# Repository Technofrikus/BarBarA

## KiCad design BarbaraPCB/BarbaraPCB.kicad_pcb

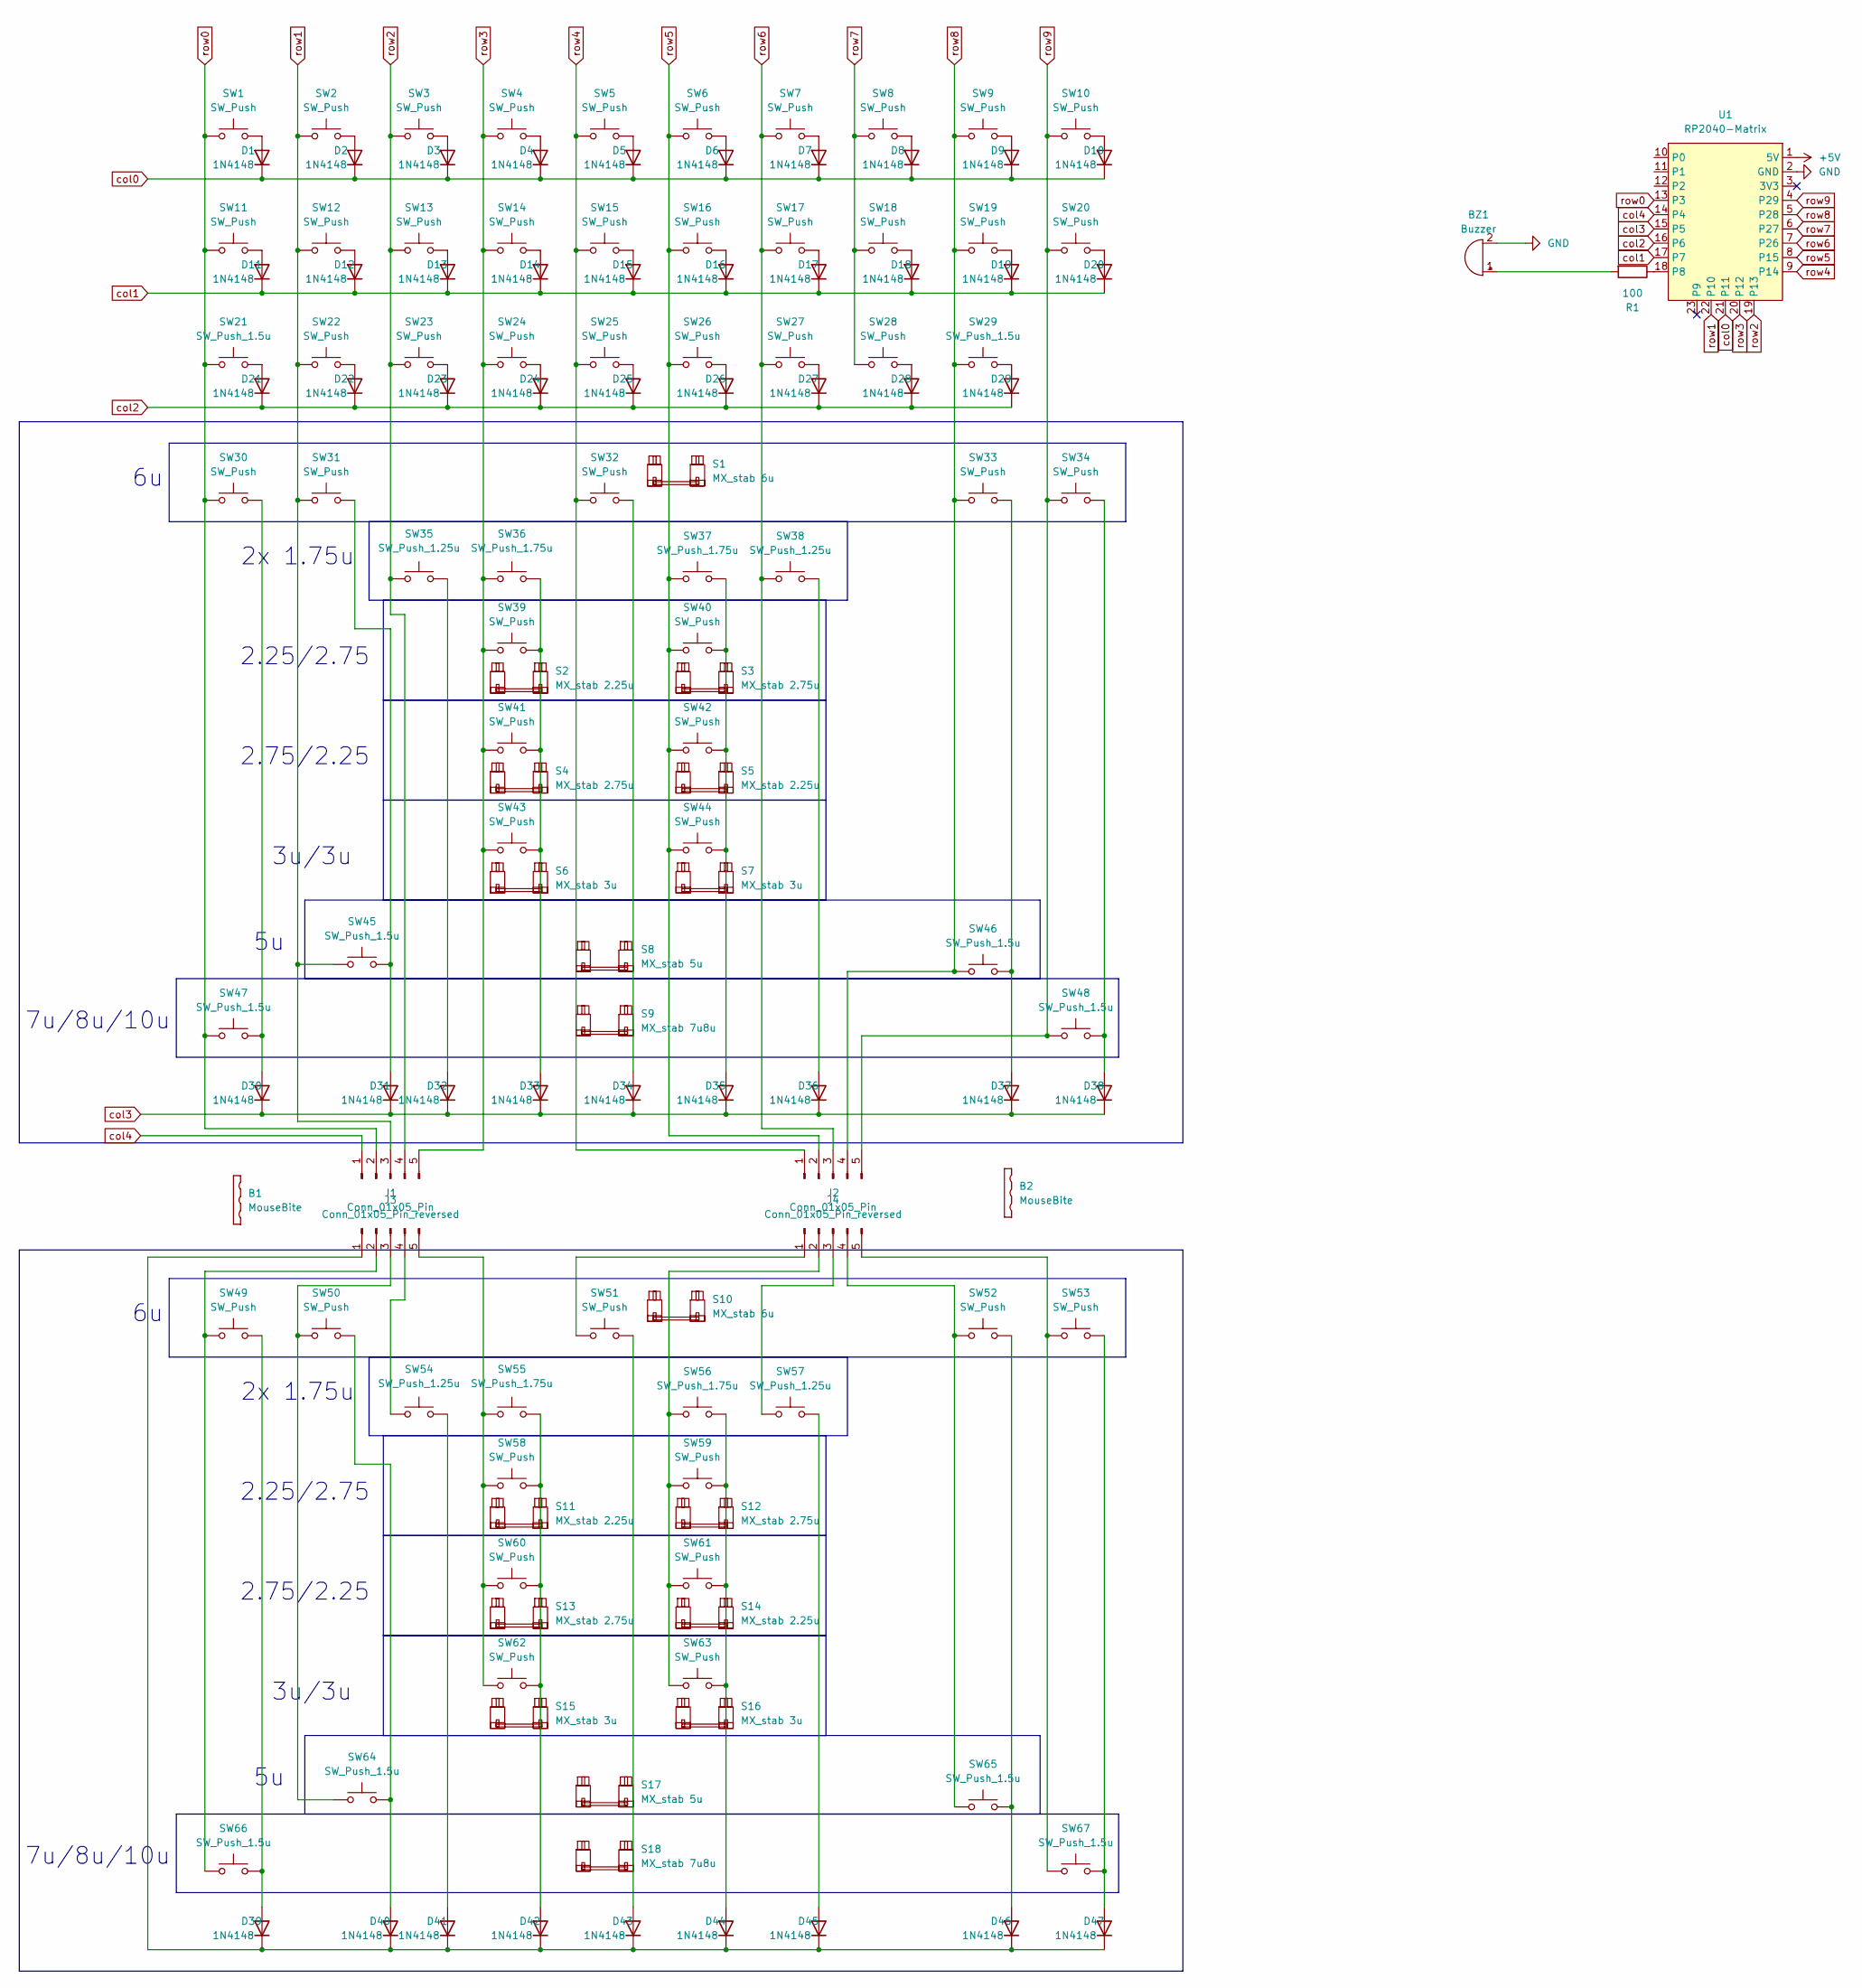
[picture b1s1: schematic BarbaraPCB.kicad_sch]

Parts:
B1, B2: MouseBite; TFmousebites_easysnap
BZ1: Buzzer; MagneticBuzzer_StarMicronics_QMB-105
D1, D2, D3, D4, D5, D6, D7, D8, D9, D10, D11, D12, D13, D14, D15, D16, D17, D18, D19, D20, D21, D22, D23, D24, D25, D26, D27, D28, D29, D30, D31, D32, D33, D34, D35, D36, D37, D38, D39, D40, D41, D42, D43, D44, D45, D46, D47: 1N4148; Diode-dual
J1, J2: Conn_01x05_Pin; PinSocket_1x05_P2.54mm_Vertical
J3, J4: Conn_01x05_Pin_reversed; PinSocket_1x05_P2.54mm_Vertical
R1: 100; Resistor-dual
S1, S10: MX_stab 6u; STAB_MX_P_6u_sizelabel
S2, S5, S11, S14: MX_stab 2.25u; STAB_MX_P_2.25u_sizelabel
S3, S4, S12, S13: MX_stab 2.75u; STAB_MX_P_2.75u_sizelabel
S6, S7, S15, S16: MX_stab 3u; STAB_MX_3u_sizelabel
S8, S17: MX_stab 5u; STAB_MX_5u
S9, S18: MX_stab 7u8u; STAB_MX_P_10u_sizelabel
SW1, SW2, SW3, SW4, SW5, SW6, SW7, SW8, SW9, SW10, SW11, SW12, SW13, SW14, SW15, SW16, SW17, SW18, SW19, SW20, SW22, SW23, SW24, SW25, SW26, SW27, SW28, SW30, SW31, SW32, SW33, SW34, SW39, SW40, SW41, SW42, SW43, SW44, SW49, SW50, SW51, SW52, SW53, SW58, SW59, SW60, SW61, SW62, SW63: SW_Push; SW_MX_1u
SW21, SW29, SW45, SW46, SW47, SW48, SW64, SW65, SW66, SW67: SW_Push_1.5u; SW_MX_1.5u
SW35, SW38, SW54, SW57: SW_Push_1.25u; SW_MX_1.25u
SW36, SW37, SW55, SW56: SW_Push_1.75u; SW_MX_1.75u
U1: RP2040-Matrix; RP2040-Gemini-BigHole

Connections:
+5V: U1.1 (5V)
GND: BZ1.2 (-), U1.2 (GND)
unnamed: BZ1.1 (+), R1.2
unnamed: D1.2 (A), SW1.2
unnamed: D2.2 (A), SW2.2
unnamed: D3.2 (A), SW3.2
unnamed: D4.2 (A), SW4.2
unnamed: D5.2 (A), SW5.2
unnamed: D6.2 (A), SW6.2
unnamed: D7.2 (A), SW7.2
unnamed: D8.2 (A), SW8.2
unnamed: D9.2 (A), SW9.2
unnamed: D10.2 (A), SW10.2
unnamed: D11.2 (A), SW11.2
unnamed: D12.2 (A), SW12.2
unnamed: D13.2 (A), SW13.2
unnamed: D14.2 (A), SW14.2
unnamed: D15.2 (A), SW15.2
unnamed: D16.2 (A), SW16.2
unnamed: D17.2 (A), SW17.2
unnamed: D18.2 (A), SW18.2
unnamed: D19.2 (A), SW19.2
unnamed: D20.2 (A), SW20.2
unnamed: D21.2 (A), SW21.2
unnamed: D22.2 (A), SW22.2
unnamed: D23.2 (A), SW23.2
unnamed: D24.2 (A), SW24.2
unnamed: D25.2 (A), SW25.2
unnamed: D26.2 (A), SW26.2
unnamed: D27.2 (A), SW27.2
unnamed: D28.2 (A), SW28.2
unnamed: D29.2 (A), SW29.2
unnamed: D30.2 (A), SW30.2, SW47.2
unnamed: D31.2 (A), SW31.2, SW45.2
unnamed: D32.2 (A), SW35.2
unnamed: D33.2 (A), SW36.2, SW39.2, SW41.2, SW43.2
unnamed: D34.2 (A), SW32.2
unnamed: D35.2 (A), SW37.2, SW40.2, SW42.2, SW44.2
unnamed: D36.2 (A), SW38.2
unnamed: D37.2 (A), SW33.2, SW46.2
unnamed: D38.2 (A), SW34.2, SW48.2
unnamed: D39.2 (A), SW49.2, SW66.2
unnamed: D39.1 (K), D40.1 (K), D41.1 (K), D42.1 (K), D43.1 (K), D44.1 (K), D45.1 (K), D46.1 (K), D47.1 (K), J3.1 (Pin_5)
unnamed: D40.2 (A), SW50.2, SW64.2
unnamed: D41.2 (A), SW54.2
unnamed: D42.2 (A), SW55.2, SW58.2, SW60.2, SW62.2
unnamed: D43.2 (A), SW51.2
unnamed: D44.2 (A), SW56.2, SW59.2, SW61.2, SW63.2
unnamed: D45.2 (A), SW57.2
unnamed: D46.2 (A), SW52.2, SW65.2
unnamed: D47.2 (A), SW53.2, SW67.2
unnamed: J3.5 (Pin_1), SW55.1, SW58.1, SW60.1, SW62.1
unnamed: J3.4 (Pin_2), SW54.1
unnamed: J3.3, SW50.1, SW64.1
unnamed: J3.2 (Pin_4), SW49.1, SW66.1
unnamed: J4.5 (Pin_1), SW53.1, SW67.1
unnamed: J4.4 (Pin_2), SW52.1, SW65.1
unnamed: J4.3, SW57.1
unnamed: J4.2 (Pin_4), SW56.1, SW59.1, SW61.1, SW63.1
unnamed: J4.1 (Pin_5), SW51.1
unnamed: R1.1, U1.18 (P8)
col0: D1.1 (K), D2.1 (K), D3.1 (K), D4.1 (K), D5.1 (K), D6.1 (K), D7.1 (K), D8.1 (K), D9.1 (K), D10.1 (K), U1.21 (P11)
col1: D11.1 (K), D12.1 (K), D13.1 (K), D14.1 (K), D15.1 (K), D16.1 (K), D17.1 (K), D18.1 (K), D19.1 (K), D20.1 (K), U1.17 (P7)
col2: D21.1 (K), D22.1 (K), D23.1 (K), D24.1 (K), D25.1 (K), D26.1 (K), D27.1 (K), D28.1 (K), D29.1 (K), U1.16 (P6)
col3: D30.1 (K), D31.1 (K), D32.1 (K), D33.1 (K), D34.1 (K), D35.1 (K), D36.1 (K), D37.1 (K), D38.1 (K), U1.15 (P5)
col4: J1.1, U1.14 (P4)
row0: J1.2, SW1.1, SW11.1, SW21.1, SW30.1, SW47.1, U1.13 (P3)
row1: J1.3, SW2.1, SW12.1, SW22.1, SW31.1, SW45.1, U1.22 (P10)
row2: J1.4, SW3.1, SW13.1, SW23.1, SW35.1, U1.19 (P13)
row3: J1.5, SW4.1, SW14.1, SW24.1, SW36.1, SW39.1, SW41.1, SW43.1, U1.20 (P12)
row4: J2.1, SW5.1, SW15.1, SW25.1, SW32.1, U1.9 (P14)
row5: J2.2, SW6.1, SW16.1, SW26.1, SW37.1, SW40.1, SW42.1, SW44.1, U1.8 (P15)
row6: J2.3, SW7.1, SW17.1, SW27.1, SW38.1, U1.7 (P26)
row7: SW8.1, SW18.1, SW28.1, U1.6 (P27)
row8: J2.4, SW9.1, SW19.1, SW29.1, SW33.1, SW46.1, U1.5 (P28)
row9: J2.5, SW10.1, SW20.1, SW34.1, SW48.1, U1.4 (P29)

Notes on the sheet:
2.75/2.25
3u/3u
2.25/2.75
7u/8u/10u
2x 1.75u

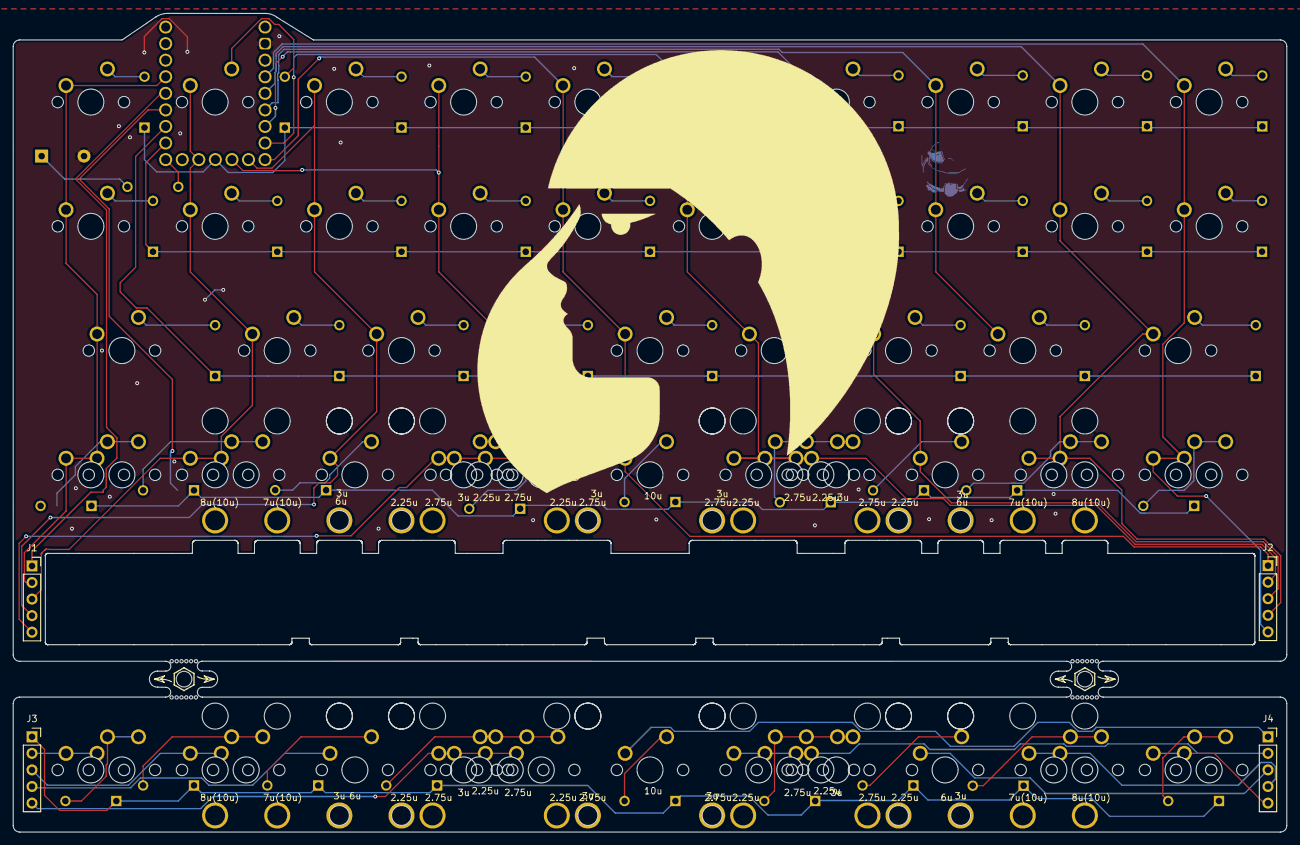
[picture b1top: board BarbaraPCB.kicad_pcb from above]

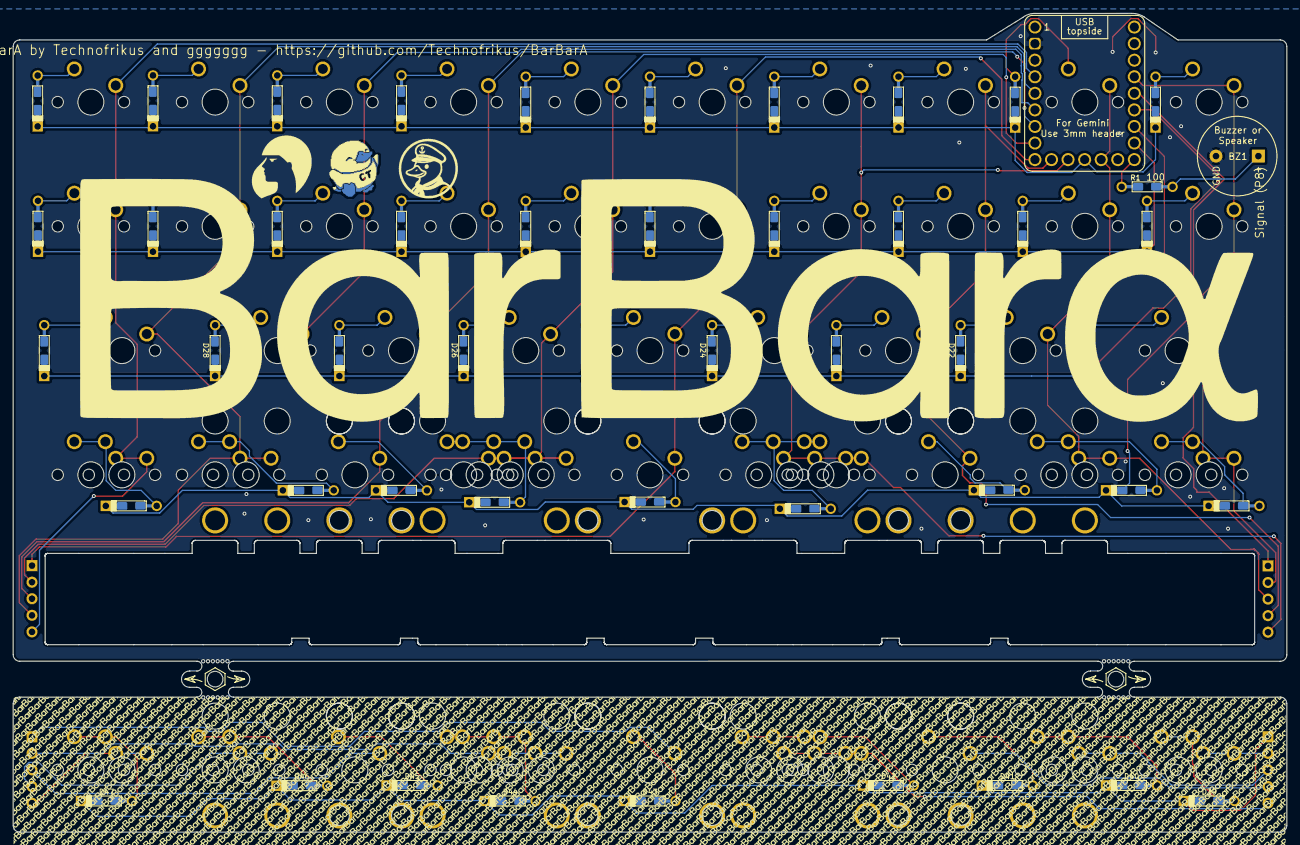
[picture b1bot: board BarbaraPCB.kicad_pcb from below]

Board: 2 copper layers, 195.3 x 125.5 mm, 146 parts (54 on the bottom side), 75 nets.

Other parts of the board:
Ref**: Val**; BarBara Kopf only 3,5u
Ref**#2: Val**; BarBara minimal Barbar
Ref**#3: Val**; Moinboards new logo 10mm
Ref**#4: Val**; BarBara minimal only big
Ref**#5: Val**; BarBara Kopf only 1u

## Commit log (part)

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2026-05-13 Soundbauteile hinzugefügt
2026-05-24 Silk und diverse Kleinigkeiten. Productionready?!
2026-05-31 Simplified audio-part. Not amp or transistor needed.
2026-06-02 Removed the thin parts in the plate part of the PCB, were too small for manufacturing. Ordered first Protos.
